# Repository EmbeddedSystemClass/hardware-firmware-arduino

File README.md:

hardware-firmware-arduino
=========================

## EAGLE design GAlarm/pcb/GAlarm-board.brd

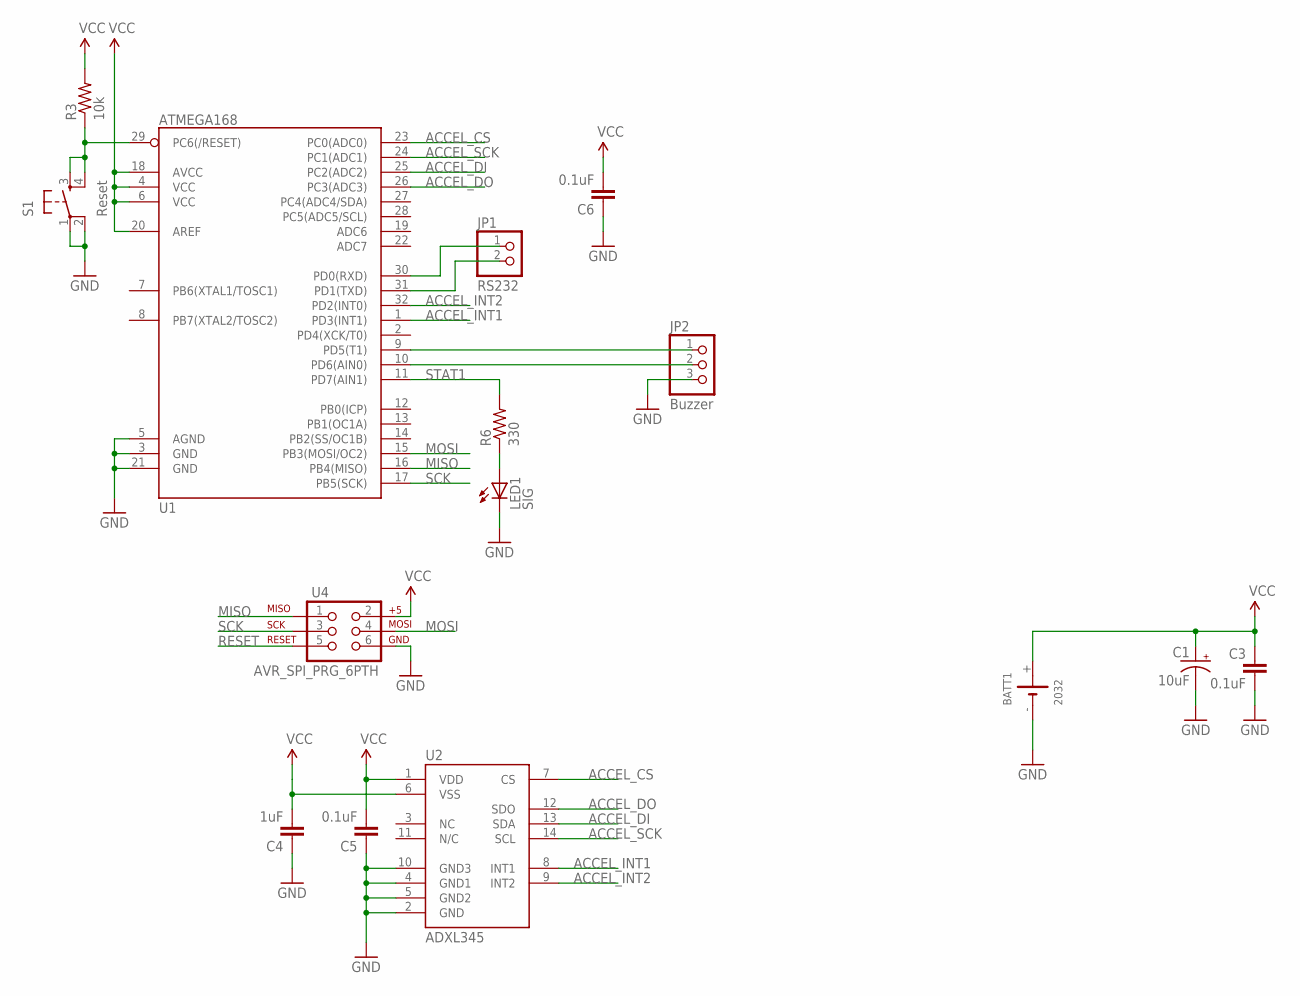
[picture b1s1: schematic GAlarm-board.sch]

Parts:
BATT1: 2032; 2032_SMD
C1: 10uF; EIA3216
C3, C5, C6: 0.1uF; 0603-CAP
C4: 1uF; 0805
JP1: RS232; 1X02
JP2: Buzzer; 1X03
LED1: SIG; LED-0603
R3: 10k; 0603-RES
R6: 330; 0603-RES
S1: Reset; TACTILE_SWITCH_SMD
U1: ATMEGA168; TQFP32-08
U2: ADXL345; LGA14
U4: AVR_SPI_PRG_6PTH; 2X3

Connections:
ACCEL_CS: U1.23 (PC0(ADC0)), U2.7 (CS)
ACCEL_DI: U1.25 (PC2(ADC2)), U2.13 (SDA)
ACCEL_DO: U1.26 (PC3(ADC3)), U2.12 (SDO)
ACCEL_INT1: U1.1 (PD3(INT1)), U2.8 (INT1)
ACCEL_INT2: U1.32 (PD2(INT0)), U2.9 (INT2)
ACCEL_SCK: U1.24 (PC1(ADC1)), U2.14 (SCL)
GND: BATT1.-, C1.C (-), C3.2, C4.1, C5.1, C6.1, JP2.3, LED1.C, S1.1, S1.2, U1.3 (GND), U1.5 (AGND), U1.21 (GND), U2.2 (GND), U2.4 (GND1), U2.5 (GND2), U2.10 (GND3), U4.6
MISO: U1.16 (PB4(MISO)), U4.1
MOSI: U1.15 (PB3(MOSI/OC2)), U4.4
unnamed: LED1.A, R6.1
unnamed: JP2.2, U1.10 (PD6(AIN0))
unnamed: JP1.1, U1.30 (PD0(RXD))
unnamed: JP1.2, U1.31 (PD1(TXD))
unnamed: JP2.1, U1.9 (PD5(T1))
RESET: R3.1, S1.3, S1.4, U1.29 (PC6(/RESET)), U4.5
SCK: U1.17 (PB5(SCK)), U4.3
STAT1: R6.2, U1.11 (PD7(AIN1))
VCC: BATT1.+, C1.A (+), C3.1, C4.2, C5.2, C6.2, R3.2, U1.4 (VCC), U1.6 (VCC), U1.18 (AVCC), U1.20 (AREF), U2.1 (VDD), U2.6 (VSS), U4.2

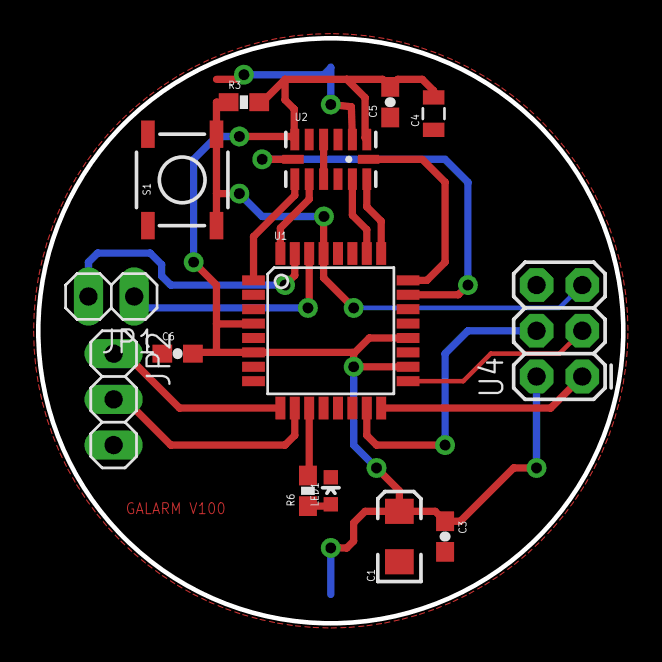
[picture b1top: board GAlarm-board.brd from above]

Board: 2 copper layers, 32.5 x 32.5 mm, 15 parts (1 on the bottom side), 18 nets.

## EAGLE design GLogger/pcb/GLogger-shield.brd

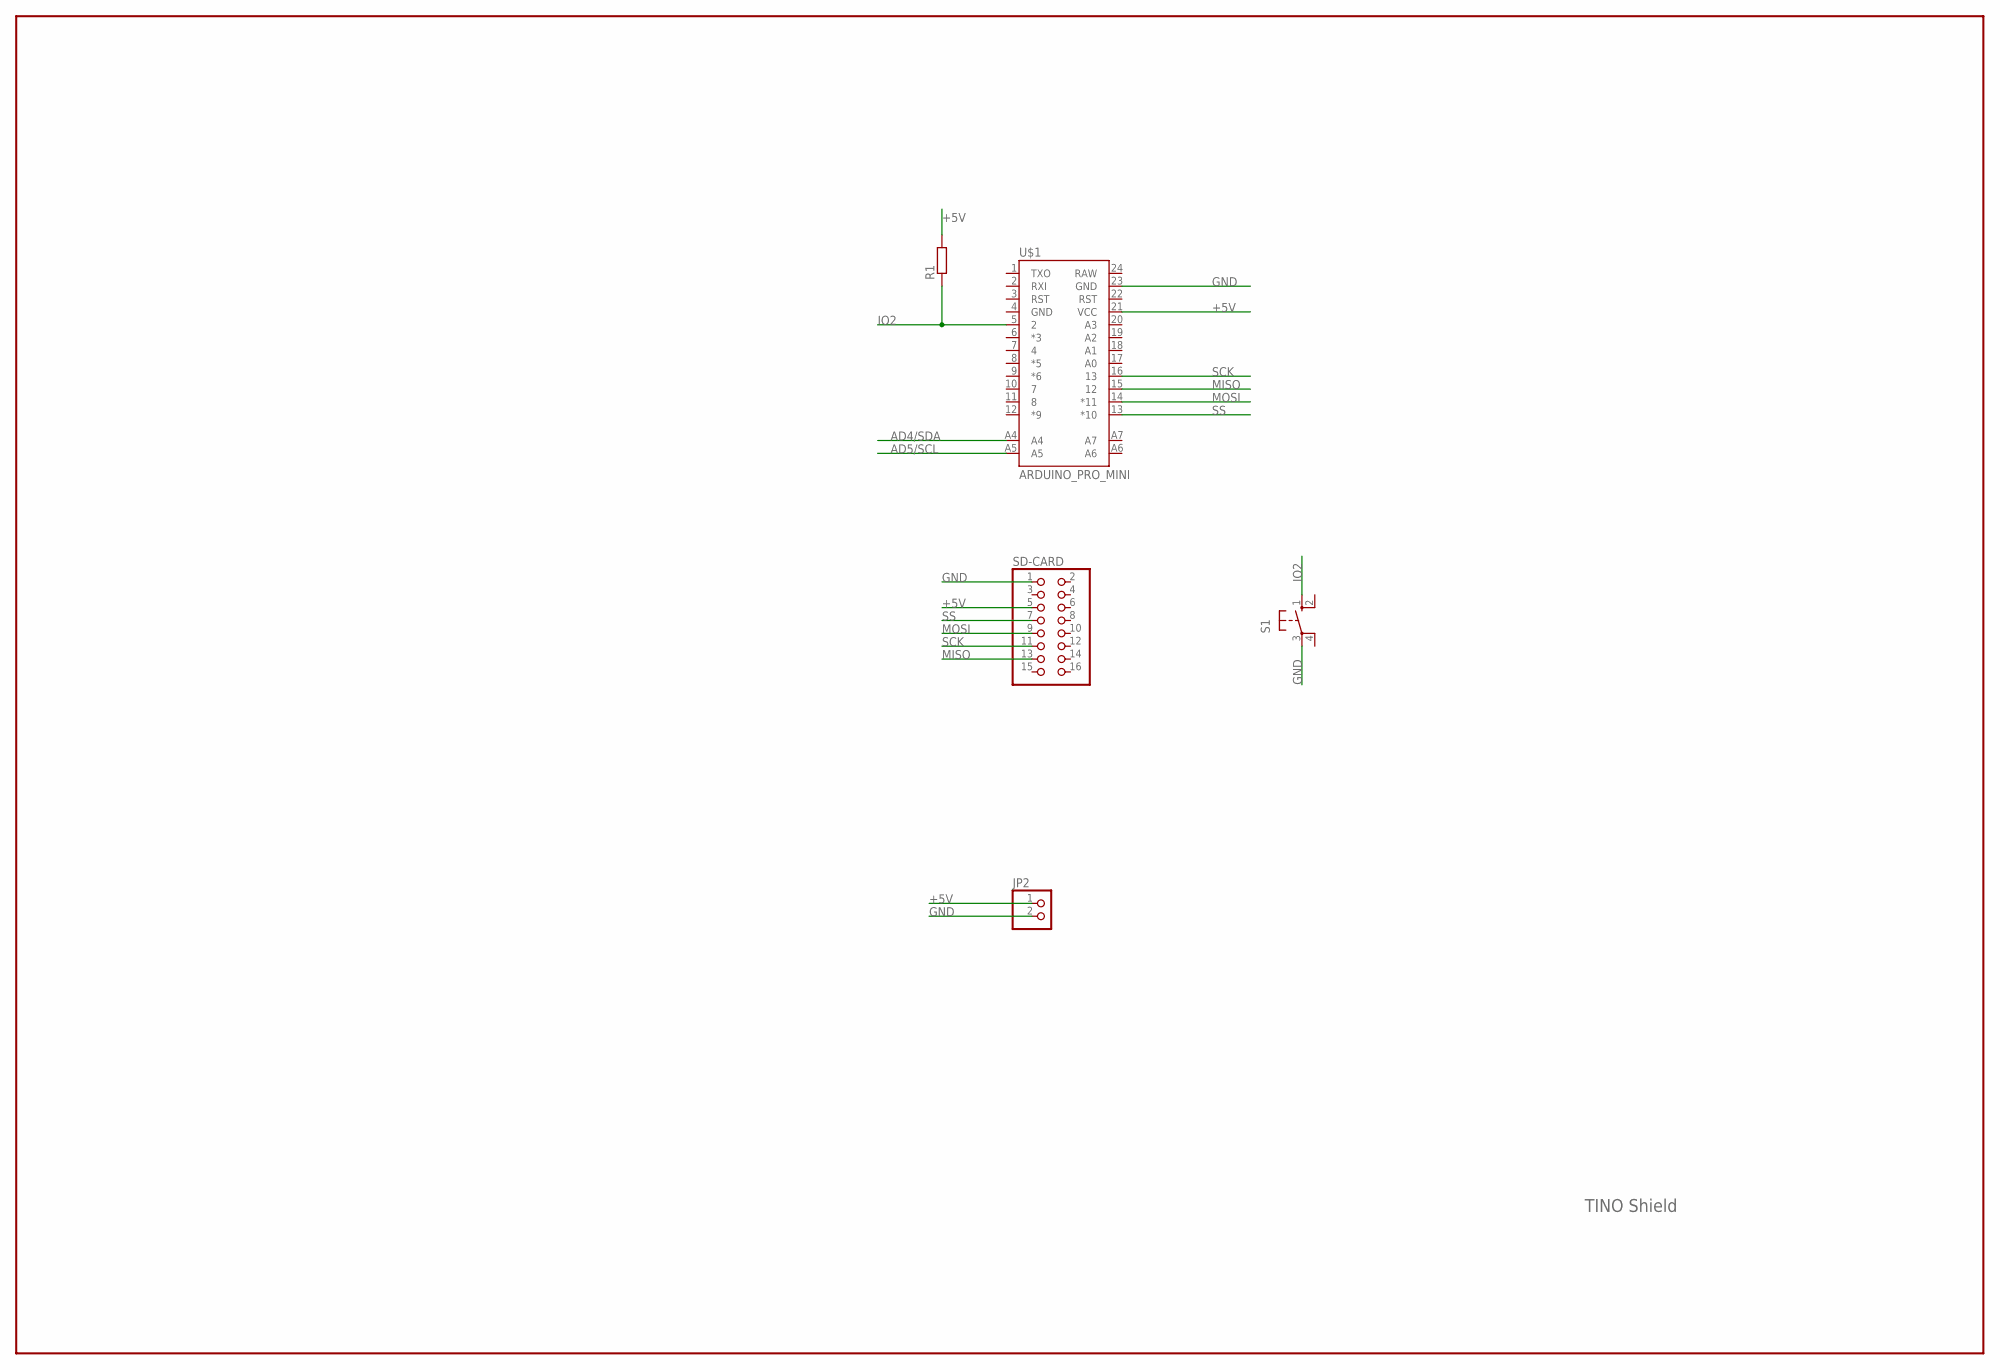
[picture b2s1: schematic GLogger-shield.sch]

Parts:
JP2: PINHD-1X2; 1X02
R1: R-EU_0207/10; 0207/10
S1: 40-XX-ROUND; B3F-40XX-ROUND
SD-CARD: PINHD-2X8; 2X08
U$1: ARDUINO_PRO_MINI

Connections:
+5V: JP2.1, R1.2, SD-CARD.5, U$1.21 (VCC)
AD4/SDA: U$1.A4
AD5/SCL: U$1.A5
GND: JP2.2, S1.3, SD-CARD.1, U$1.23 (GND)
IO2: R1.1, S1.1 (S), U$1.5 (2)
MISO: SD-CARD.13, U$1.15 (12)
MOSI: SD-CARD.9, U$1.14 (*11)
SCK: SD-CARD.11, U$1.16 (13)
SS: SD-CARD.7, U$1.13 (*10)

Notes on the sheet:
TINO Shield

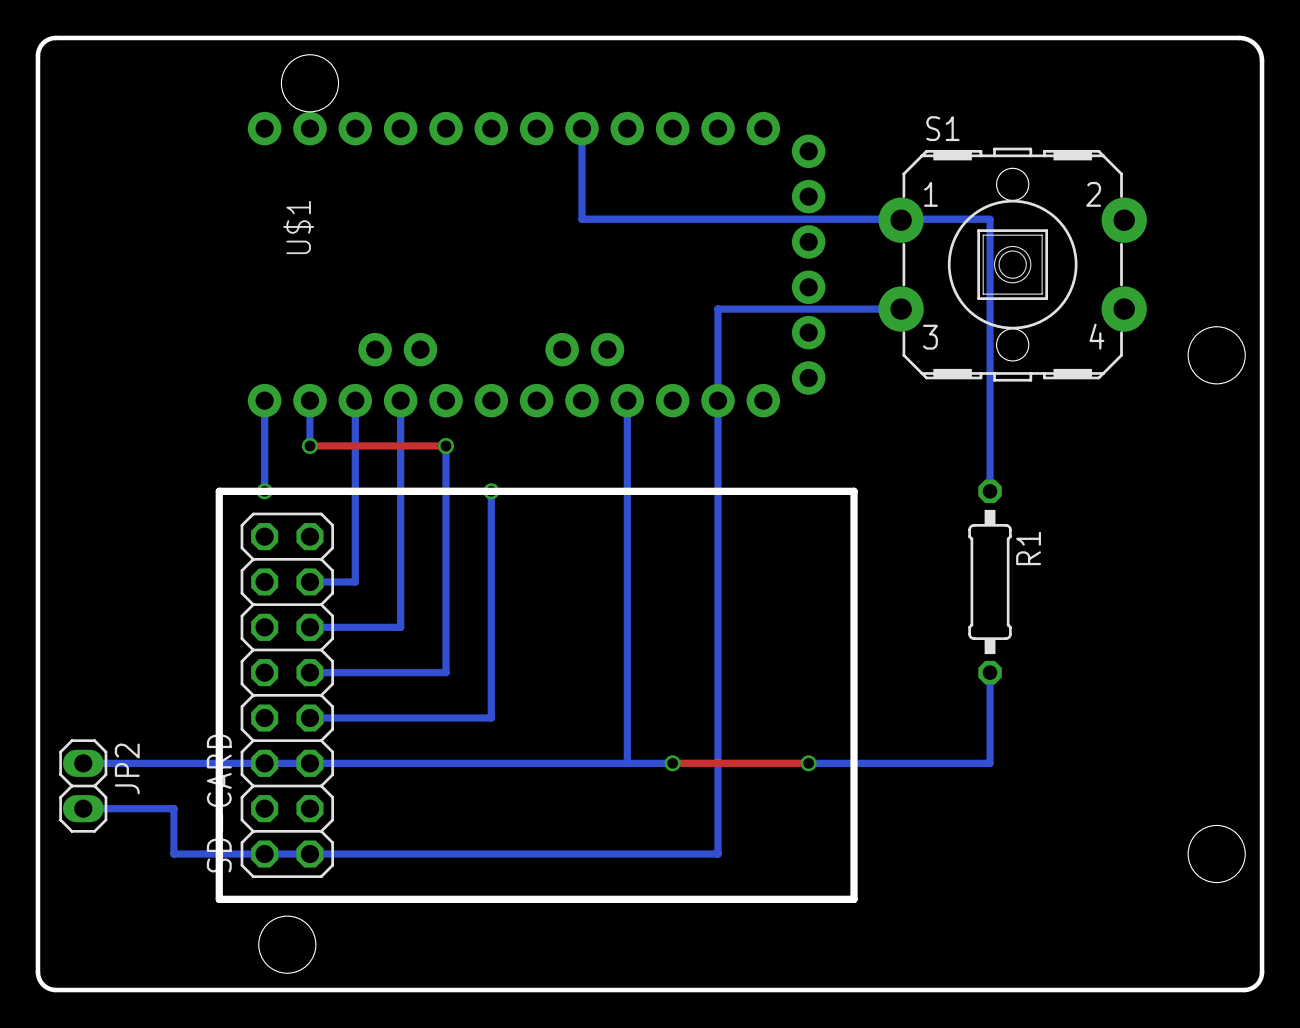
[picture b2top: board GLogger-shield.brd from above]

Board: 2 copper layers, 68.6 x 53.3 mm, 5 parts (0 on the bottom side), 7 nets.

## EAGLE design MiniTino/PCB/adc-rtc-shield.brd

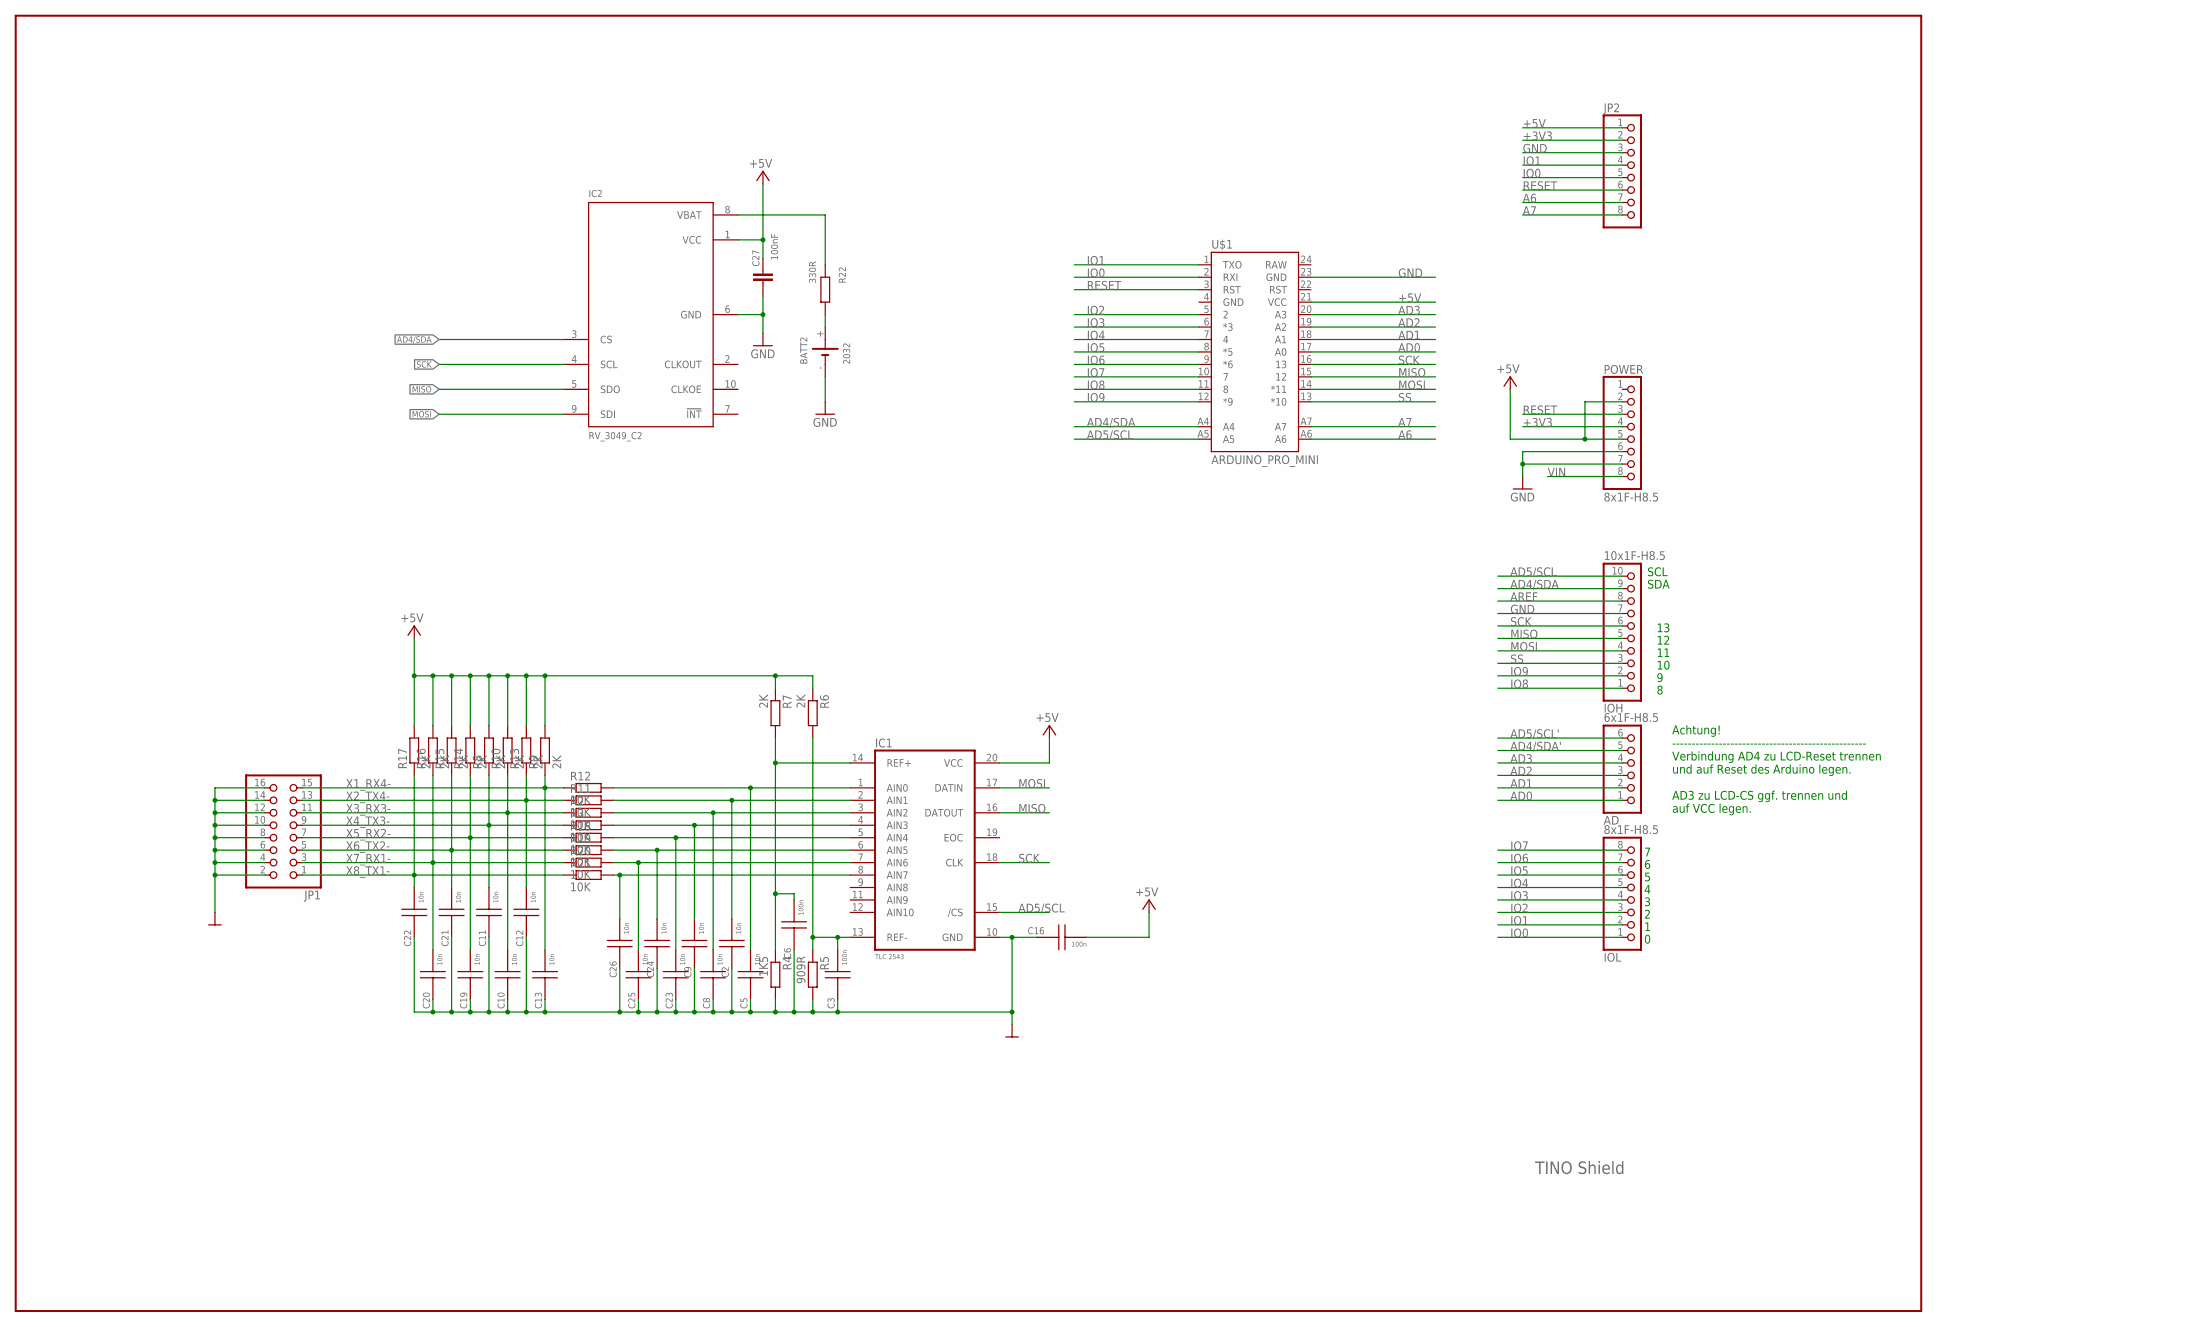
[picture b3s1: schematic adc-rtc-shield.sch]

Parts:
AD: 6x1F-H8.5; 1X06
BATT2: 2032; 2032_SMD
C2, C5, C8, C9, C10, C11, C12, C13, C19, C20, C21, C22, C23, C24, C25, C26: 10n; 0805-C
C3, C6, C16: 100n; 0805-C
C27: 100nF; C0603
IC1: TLC2543; DIL_20
IC2: RV_3049_C2; 5X3.2_10
IOH: 10x1F-H8.5; 1X10
IOL: 8x1F-H8.5; 1X08
JP1: PINHD-2X8/90; 2X08/90
JP2: PINHD-1X8/90; 1X08/90
POWER: 8x1F-H8.5; 1X08
R2, R3, R11, R12, R18, R19, R20, R21: 10K; R0603
R4: 1K5; R0603
R5: 909R; R0603
R6, R7, R8, R9, R10, R13, R14, R15, R16, R17: 2K; R0603
R22: 330R; R0603
U$1: ARDUINO_PRO_MINI

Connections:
+3V3: JP2.2, POWER.4
+5V: C16.2, C27.1, IC1.20 (VCC), IC2.1 (VCC), JP2.1, POWER.2, POWER.5, R6.1, R7.1, R8.2, R9.2, R10.2, R13.2, R14.2, R15.2, R16.2, R17.2, U$1.21 (VCC)
+BAT: BATT2.+, R22.1
A6: JP2.7, U$1.A6
A7: JP2.8, U$1.A7
AD0: AD.1, U$1.17 (A0)
AD1: AD.2, U$1.18 (A1)
AD2: AD.3, U$1.19 (A2)
AD3: AD.4, U$1.20 (A3)
AD4/SDA: IC2.3 (CS), IOH.9, U$1.A4
AD4/SDA': AD.5
AD5/SCL: IC1.15 (/CS), IOH.10, U$1.A5
AD5/SCL': AD.6
AREF: IOH.8
GND: BATT2.-, C2.1, C3.1, C5.1, C6.1, C8.1, C9.1, C10.1, C11.1, C12.1, C13.1, C16.1, C19.1, C20.1, C21.1, C22.1, C23.1, C24.1, C25.1, C26.1, C27.2, IC1.10 (GND), IC2.6 (GND), IOH.7, JP1.2, JP1.4, JP1.6, JP1.8, JP1.10, JP1.12, JP1.14, JP1.16, JP2.3, POWER.6, POWER.7, R4.2, R5.2, U$1.23 (GND)
IO0: IOL.1, JP2.5, U$1.2 (RXI)
IO1: IOL.2, JP2.4, U$1.1 (TXO)
IO2: IOL.3, U$1.5 (2)
IO3: IOL.4, U$1.6 (*3)
IO4: IOL.5, U$1.7 (4)
IO5: IOL.6, U$1.8 (*5)
IO6: IOL.7, U$1.9 (*6)
IO7: IOL.8, U$1.10 (7)
IO8: IOH.1, U$1.11 (8)
IO9: IOH.2, U$1.12 (*9)
MISO: IC1.16 (DATOUT), IC2.5 (SDO), IOH.5, U$1.15 (12)
MOSI: IC1.17 (DATIN), IC2.9 (SDI), IOH.4, U$1.14 (*11)
unnamed: C3.2, IC1.13 (REF-), R5.1, R6.2
unnamed: C6.2, IC1.14 (REF+), R4.1, R7.2
unnamed: C2.2, IC1.2 (AIN1), R11.2
unnamed: C8.2, IC1.3 (AIN2), R2.2
unnamed: C9.2, IC1.4 (AIN3), R3.2
unnamed: C5.2, IC1.1 (AIN0), R12.2
unnamed: C23.2, IC1.5 (AIN4), R18.2
unnamed: C24.2, IC1.6 (AIN5), R19.2
unnamed: C25.2, IC1.7 (AIN6), R20.2
unnamed: C26.2, IC1.8 (AIN7), R21.2
unnamed: IC2.8 (VBAT), R22.2
RESET: JP2.6, POWER.3, U$1.3 (RST)
SCK: IC1.18 (CLK), IC2.4 (SCL), IOH.6, U$1.16 (13)
SS: IOH.3, U$1.13 (*10)
VIN: POWER.8
X1_RX4-: C13.2, JP1.15, R9.1, R12.1
X2_TX4-: C12.2, JP1.13, R11.1, R13.1
X3_RX3-: C10.2, JP1.11, R2.1, R10.1
X4_TX3-: C11.2, JP1.9, R3.1, R8.1
X5_RX2-: C19.2, JP1.7, R14.1, R18.1
X6_TX2-: C21.2, JP1.5, R15.1, R19.1
X7_RX1-: C20.2, JP1.3, R16.1, R20.1
X8_TX1-: C22.2, JP1.1, R17.1, R21.1

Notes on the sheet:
SDA
SCL
TINO Shield
Achtung! -------------------------------------------------- Verbindung AD4 zu LCD-Reset trennen und auf Reset des Arduino legen. AD3 zu LCD-CS ggf. trennen und auf VCC legen.

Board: 2 copper layers, 51 parts (32 on the bottom side), 46 nets, no tracks yet.

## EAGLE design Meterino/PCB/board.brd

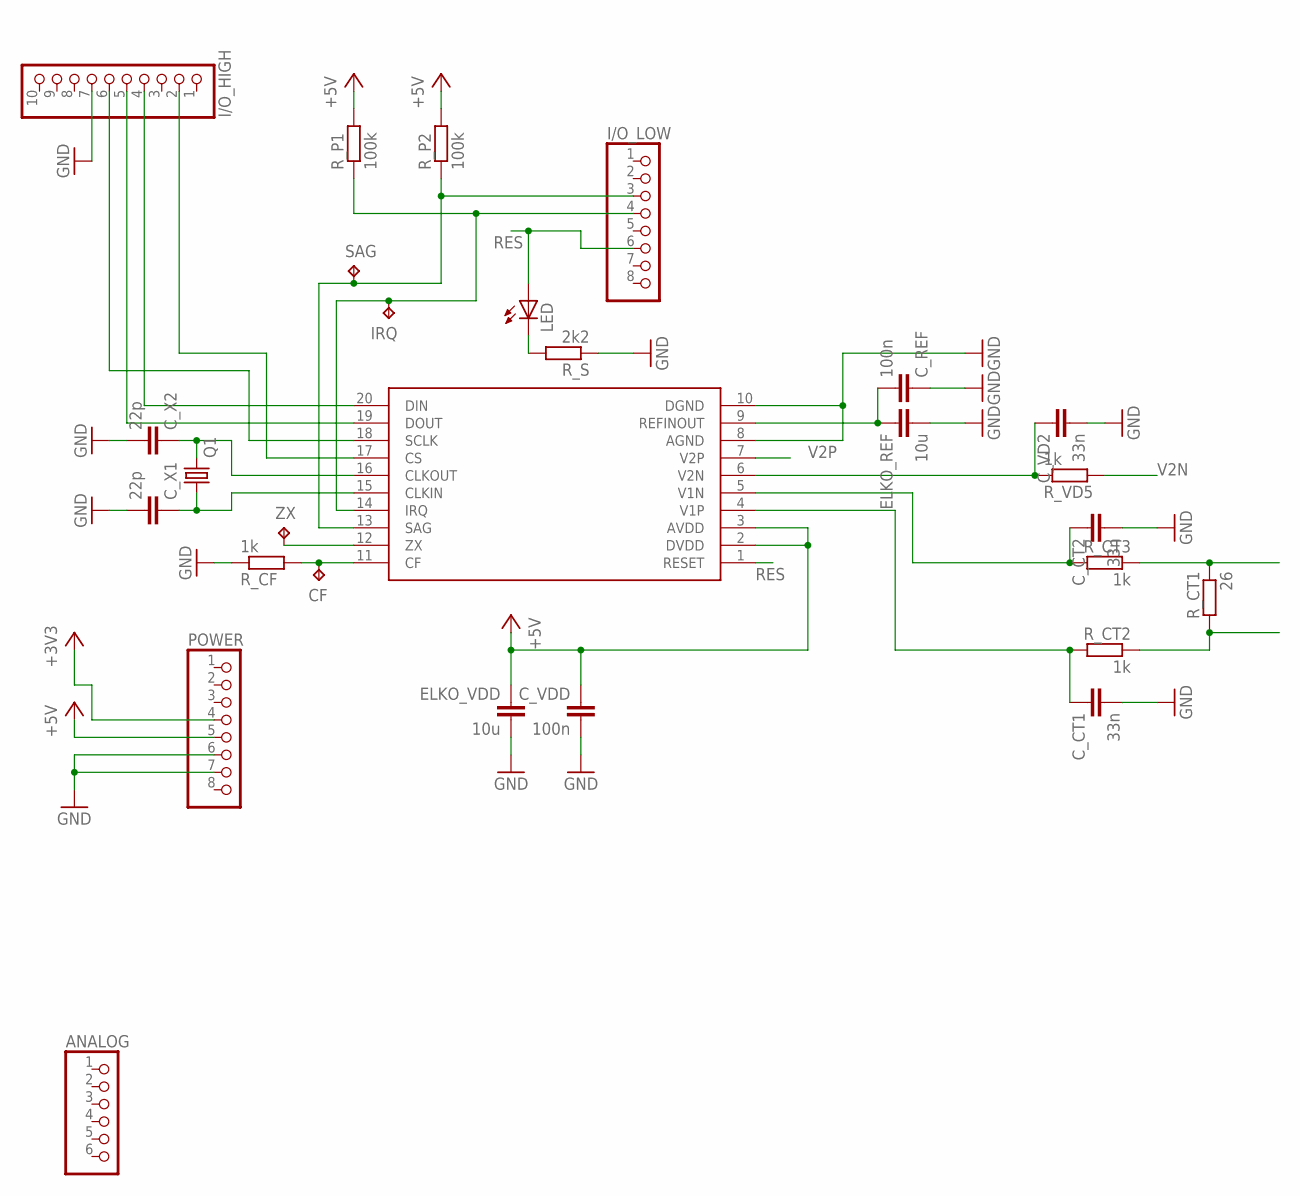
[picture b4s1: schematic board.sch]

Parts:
ANALOG: PINHD-1X6; 1X06
CF: TPPAD1-17; P1-17
C_CT1, C_CT2: 33n; C1206K
C_REF: 100n; C1206K
C_VD2: 33n; C1206K
C_VDD: 100n; C1206K
C_X1, C_X2: 22p; C1206K
ELKO_REF: 10u; C7.5B3
ELKO_VDD: 10u; C7.5B3
I/O_HIGH: PINHD-1X10TH; 1X10-TH
I/O_LOW: PINHD-1X8TH; 1X08-TH
IRQ: TPPAD1-17; P1-17
LED: LED3MM
POWER: PINHD-1X8TH; 1X08-TH
Q1: CRYSTALHC18U-V; HC18U-V
R_CF: 1k; R2010
R_CT1: 26; R2512
R_CT2, R_CT3: 1k; R2010
R_P1, R_P2: 100k; R2010
R_S: 2k2; R2512
R_VD5: 1k; R2010
SAG: TPPAD1-17; P1-17
U$1: ADE7753; SSOP20
ZX: TPPAD1-17; P1-17

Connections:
+3V3: POWER.4
+5V: C_VDD.1, ELKO_VDD.1, POWER.5, R_P1.2, R_P2.2, U$1.2 (DVDD), U$1.3 (AVDD)
GND: C_CT1.2, C_CT2.2, C_REF.1, C_VD2.2, C_VDD.2, C_X1.2, C_X2.2, ELKO_REF.2, ELKO_VDD.2, I/O_HIGH.7, POWER.6, POWER.7, R_CF.1, R_S.1, U$1.8 (AGND), U$1.10 (DGND)
unnamed: I/O_HIGH.6, U$1.18 (SCLK)
unnamed: I/O_HIGH.4, U$1.20 (DIN)
unnamed: I/O_LOW.4, IRQ.TP, R_P1.1, U$1.14 (IRQ)
unnamed: I/O_HIGH.2, U$1.17 (CS)
unnamed: C_REF.2, ELKO_REF.1, U$1.9 (REFINOUT)
unnamed: I/O_LOW.3, R_P2.1, SAG.TP, U$1.13 (SAG)
unnamed: R_CT1.2, R_CT2.1
unnamed: I/O_HIGH.5, U$1.19 (DOUT)
unnamed: LED.K (C), R_S.2
unnamed: U$1.12 (ZX), ZX.TP
unnamed: C_VD2.1, R_VD5.1, U$1.6 (V2N)
unnamed: CF.TP, R_CF.2, U$1.11 (CF)
unnamed: R_CT1.1, R_CT3.1
unnamed: C_CT2.1, R_CT3.2, U$1.5 (V1N)
unnamed: C_CT1.1, R_CT2.2, U$1.4 (V1P)
unnamed: C_X1.1, Q1.1, U$1.15 (CLKIN)
unnamed: C_X2.1, Q1.2, U$1.16 (CLKOUT)
RES: I/O_LOW.6, LED.A, U$1.1 (RESET)
V2N: R_VD5.2
V2P: U$1.7 (V2P)

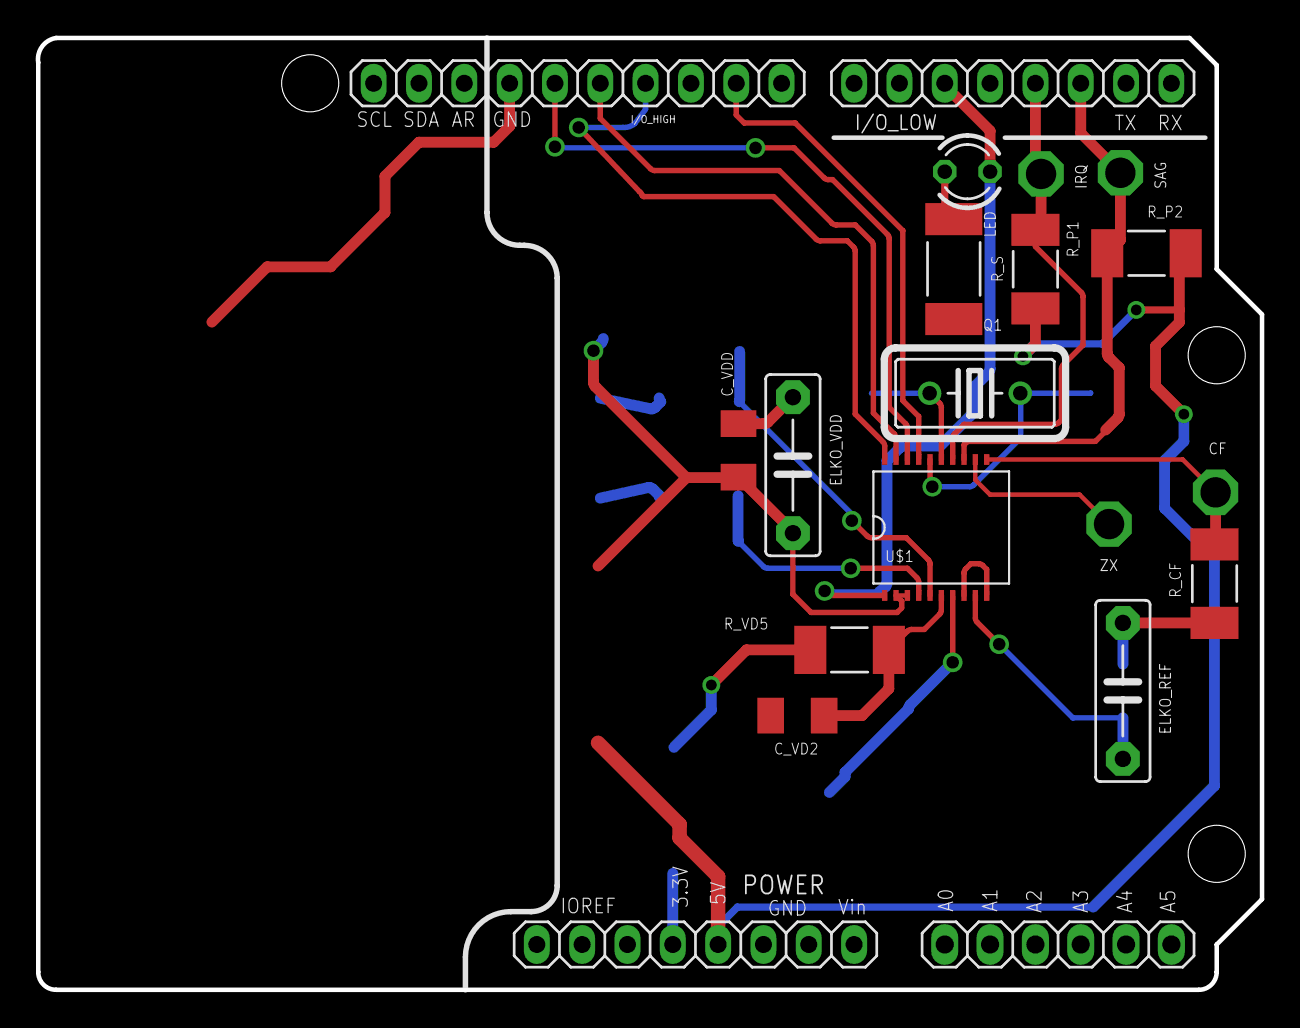
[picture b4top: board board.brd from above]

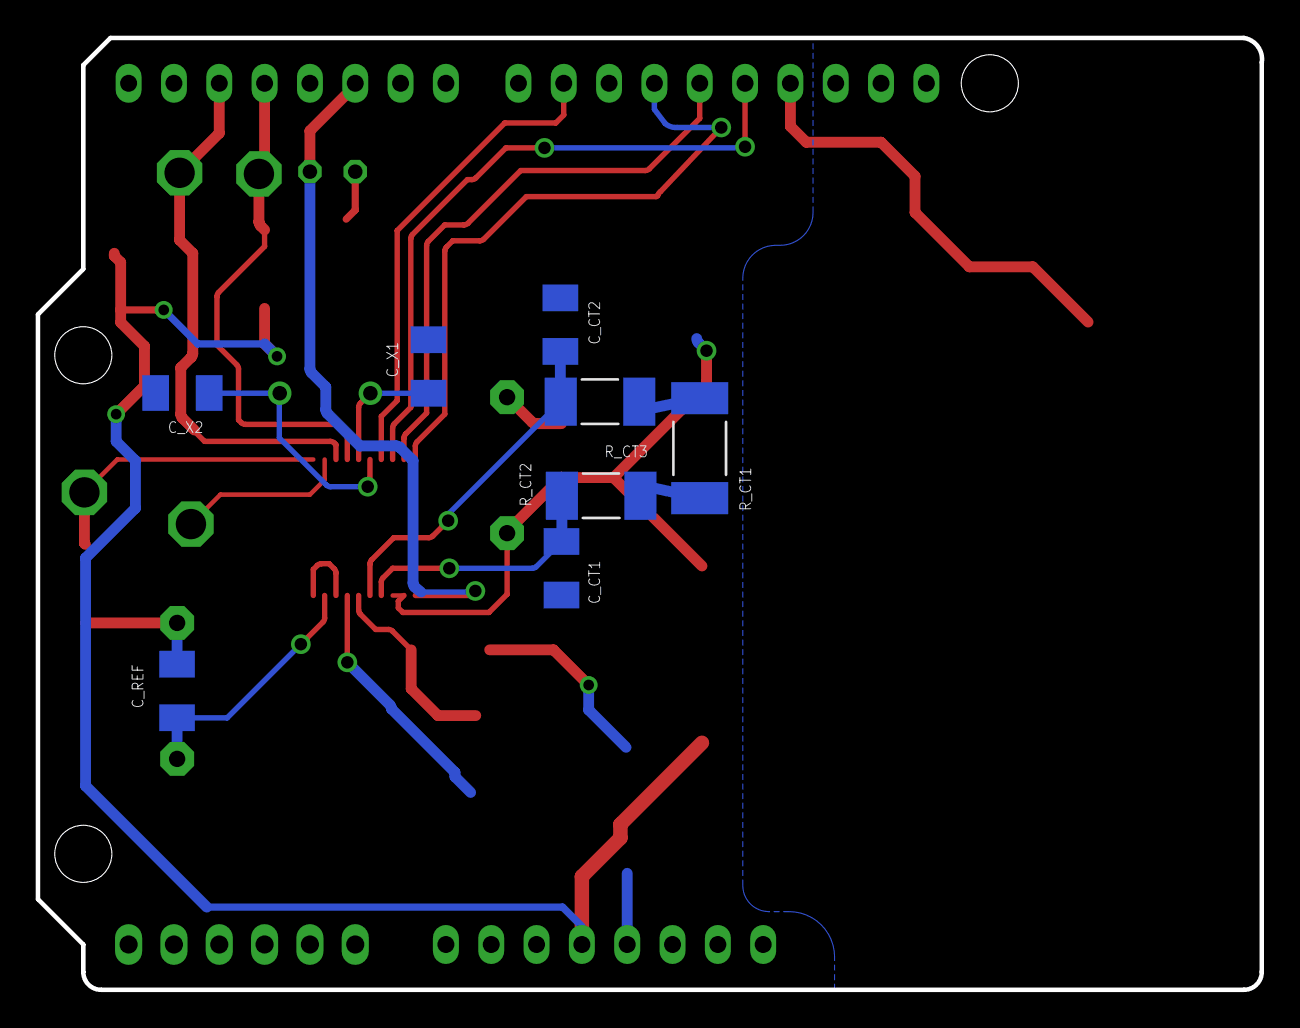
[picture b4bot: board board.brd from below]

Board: 2 copper layers, 68.6 x 53.3 mm, 28 parts (8 on the bottom side), 20 nets.

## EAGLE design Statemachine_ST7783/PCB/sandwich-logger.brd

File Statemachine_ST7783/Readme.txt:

-Display ST7783
-Temperature Sensor DS1621

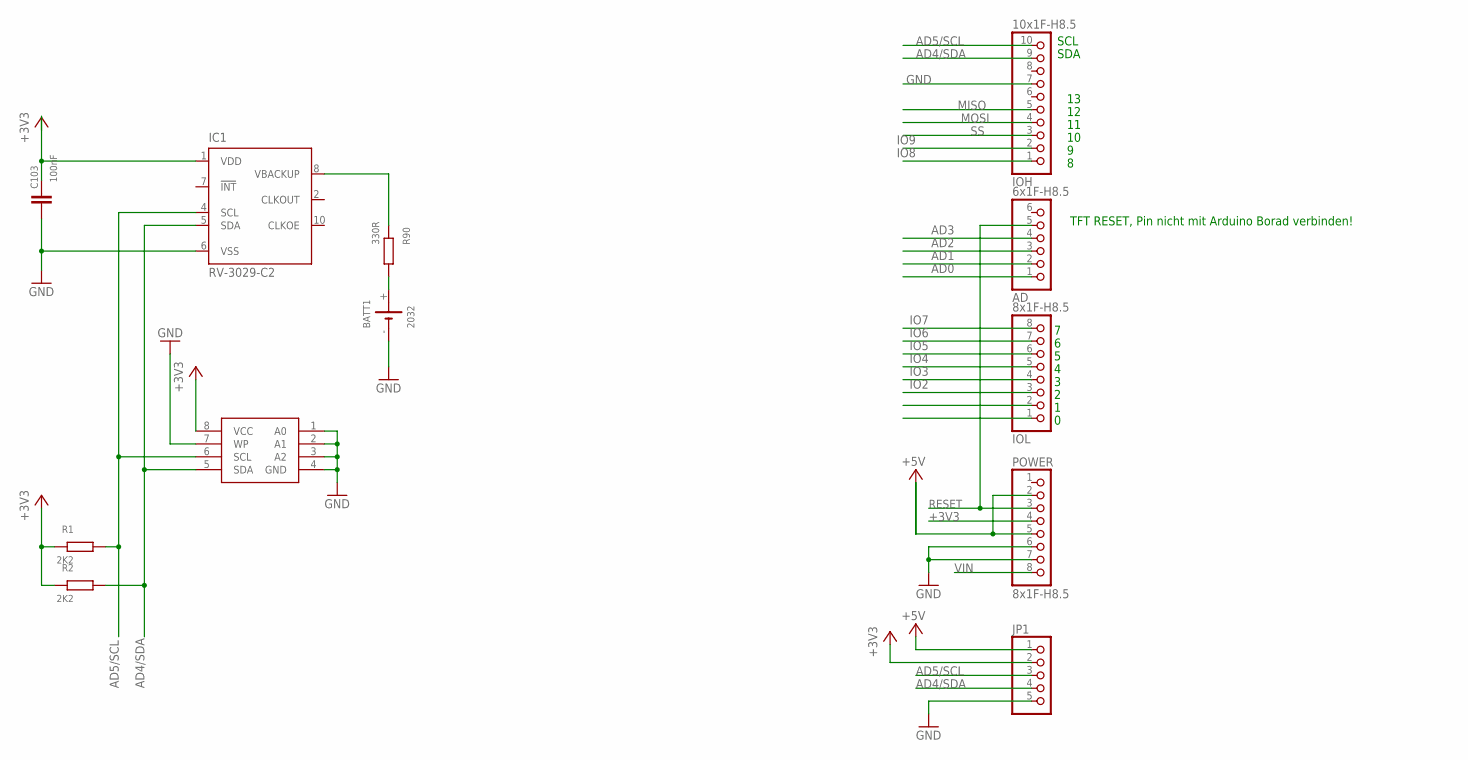
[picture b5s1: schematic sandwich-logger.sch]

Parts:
AD: 6x1F-H8.5; 1X06
BATT1: 2032; 2032_SMD
C103: 100nF; C0603
IC1: RV-3029-C2; SON-10
IC3: AT24C32; SOIC08
IOH: 10x1F-H8.5; 1X10
IOL: 8x1F-H8.5; 1X08
JP1: PINHD-1X5/90; 1X05/90
POWER: 8x1F-H8.5; 1X08
R1, R2: 2K2; R0603
R90: 330R; R0603

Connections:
+3V3: C103.1, IC1.1 (VDD), IC3.8 (VCC), JP1.2, POWER.4, R1.2, R2.2
+5V: JP1.1, POWER.2, POWER.5
AD0: AD.1
AD1: AD.2
AD2: AD.3
AD3: AD.4
AD4/SDA: IC1.5 (SDA), IC3.5 (SDA), IOH.9, JP1.4, R2.1
AD5/SCL: IC1.4 (SCL), IC3.6 (SCL), IOH.10, JP1.3, R1.1
GND: BATT1.-, C103.2, IC1.6 (VSS), IC3.1 (A0), IC3.2 (A1), IC3.3 (A2), IC3.4 (GND), IC3.7 (WP), IOH.7, JP1.5, POWER.6, POWER.7
IO2: IOL.3
IO3: IOL.4
IO4: IOL.5
IO5: IOL.6
IO6: IOL.7
IO7: IOL.8
IO8: IOH.1
IO9: IOH.2
MISO: IOH.5
MOSI: IOH.4
unnamed: BATT1.+, R90.1
unnamed: IC1.8 (VBACKUP), R90.2
RESET: AD.5, POWER.3
SS: IOH.3
VIN: POWER.8

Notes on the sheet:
SDA
SCL
TFT RESET, Pin nicht mit Arduino Borad verbinden!

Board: 2 copper layers, 12 parts (0 on the bottom side), 8 nets, no tracks yet.

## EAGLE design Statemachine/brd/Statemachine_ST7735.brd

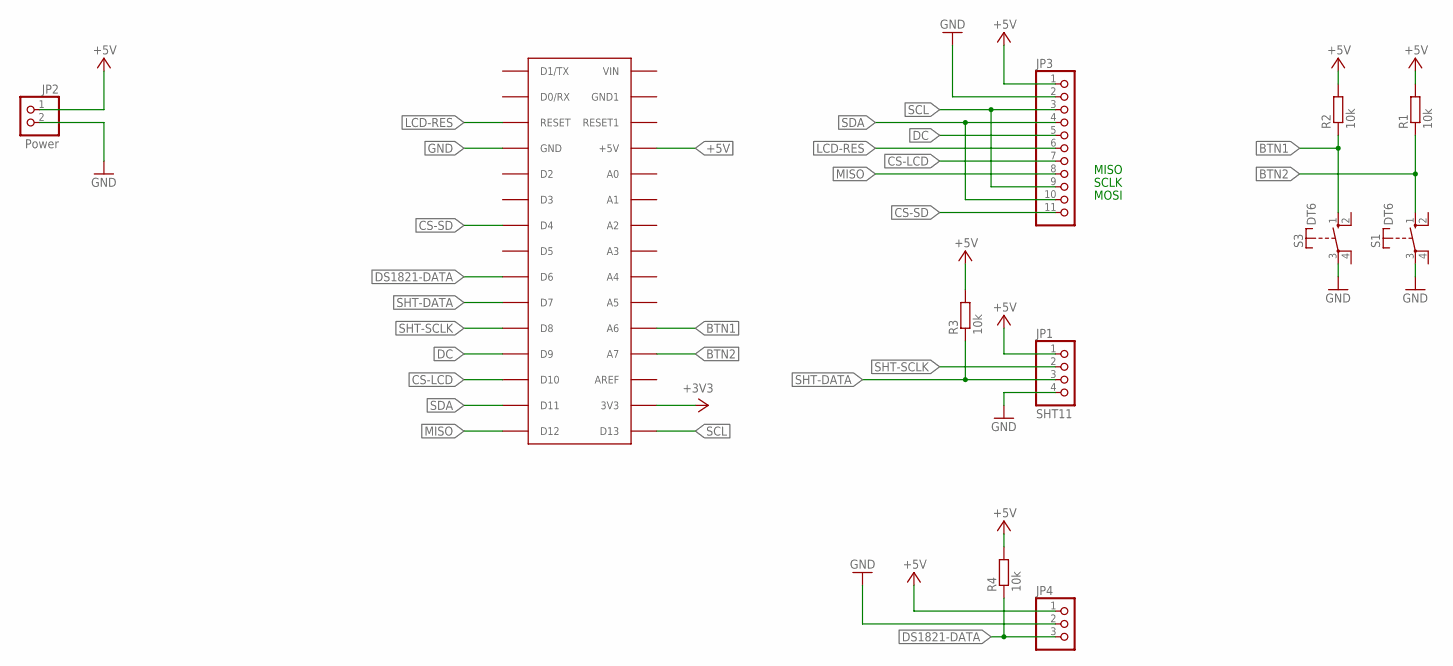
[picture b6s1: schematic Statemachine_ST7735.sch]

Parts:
JP1: SHT11; 1X04
JP2: Power; 1X02
JP3: PINHD-1X11; 1X11
JP4: PINHD-1X3; 1X03
R1, R4: 10k; 0207/10
R2, R3: 10k; 0204/7
S1, S3: DT6
U$1: ARDUINONANO; PDIP-32

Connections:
+3V3: U$1.3V3
+5V: JP1.1, JP2.1, JP3.1, JP4.1, R1.2, R2.2, R3.2, R4.2, U$1.+5V
BTN1: R2.1, S3.1 (S), U$1.A6
BTN2: R1.1, S1.1 (S), U$1.A7
CS-LCD: JP3.7, U$1.D10
CS-SD: JP3.11, U$1.D4
DC: JP3.5, U$1.D9
DS1821-DATA: JP4.3, R4.1, U$1.D6
GND: JP1.4, JP2.2, JP3.2, JP4.2, S1.3, S3.3, U$1.GND
LCD-RES: JP3.6, U$1.RESET
MISO: JP3.8, U$1.D12
SCL: JP3.3, JP3.9, U$1.D13
SDA: JP3.4, JP3.10, U$1.D11
SHT-DATA: JP1.3, R3.1, U$1.D7
SHT-SCLK: JP1.2, U$1.D8

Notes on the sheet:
MISO
SCLK
MOSI

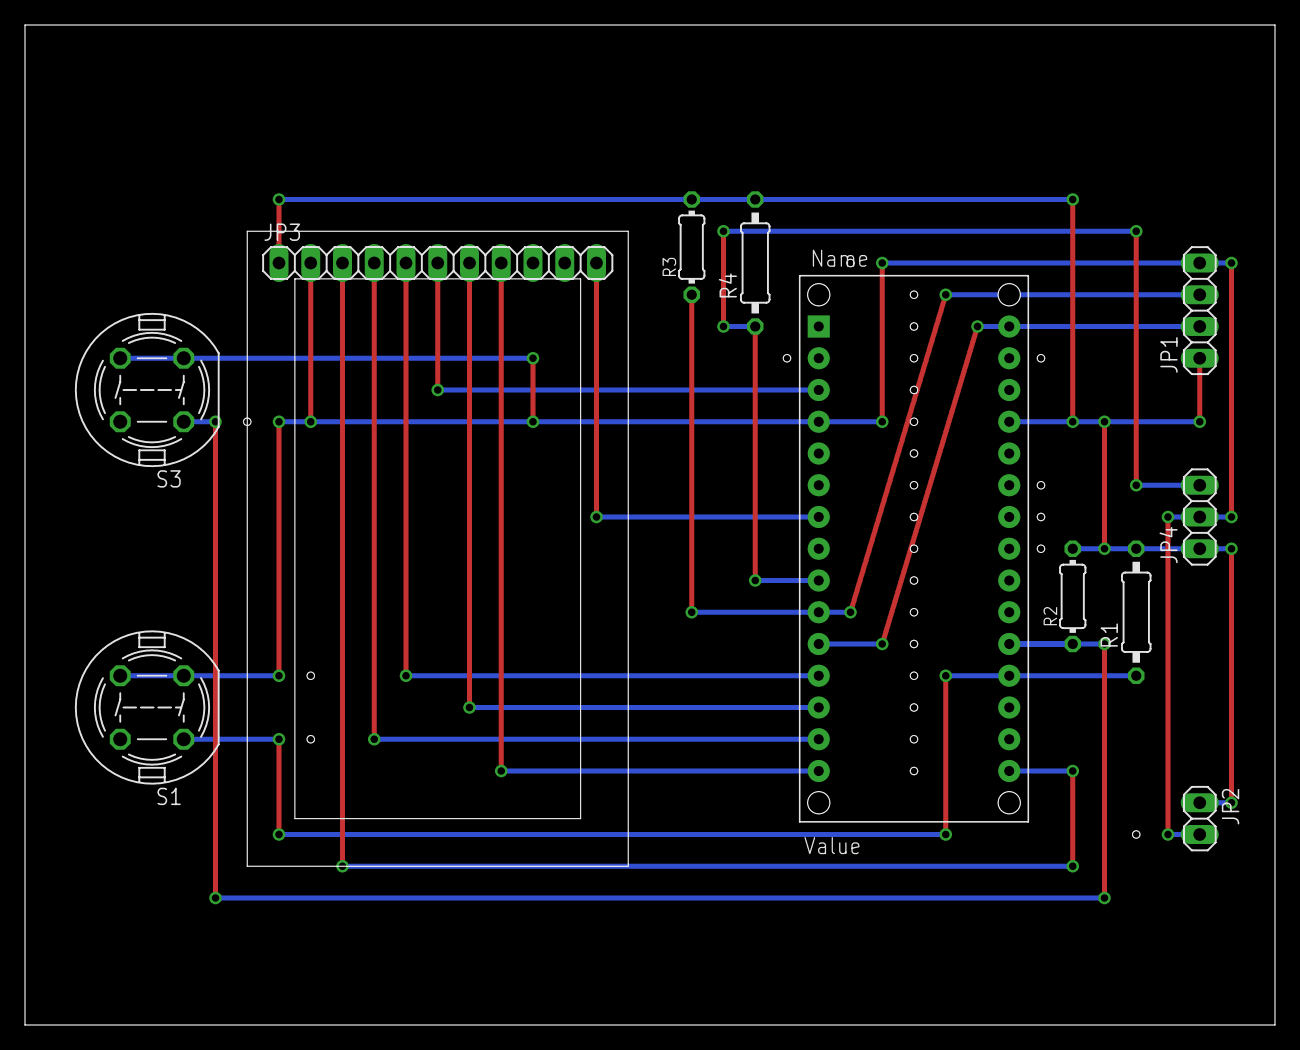
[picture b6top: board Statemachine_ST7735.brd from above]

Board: 2 copper layers, 100.0 x 80.0 mm, 11 parts (0 on the bottom side), 14 nets.

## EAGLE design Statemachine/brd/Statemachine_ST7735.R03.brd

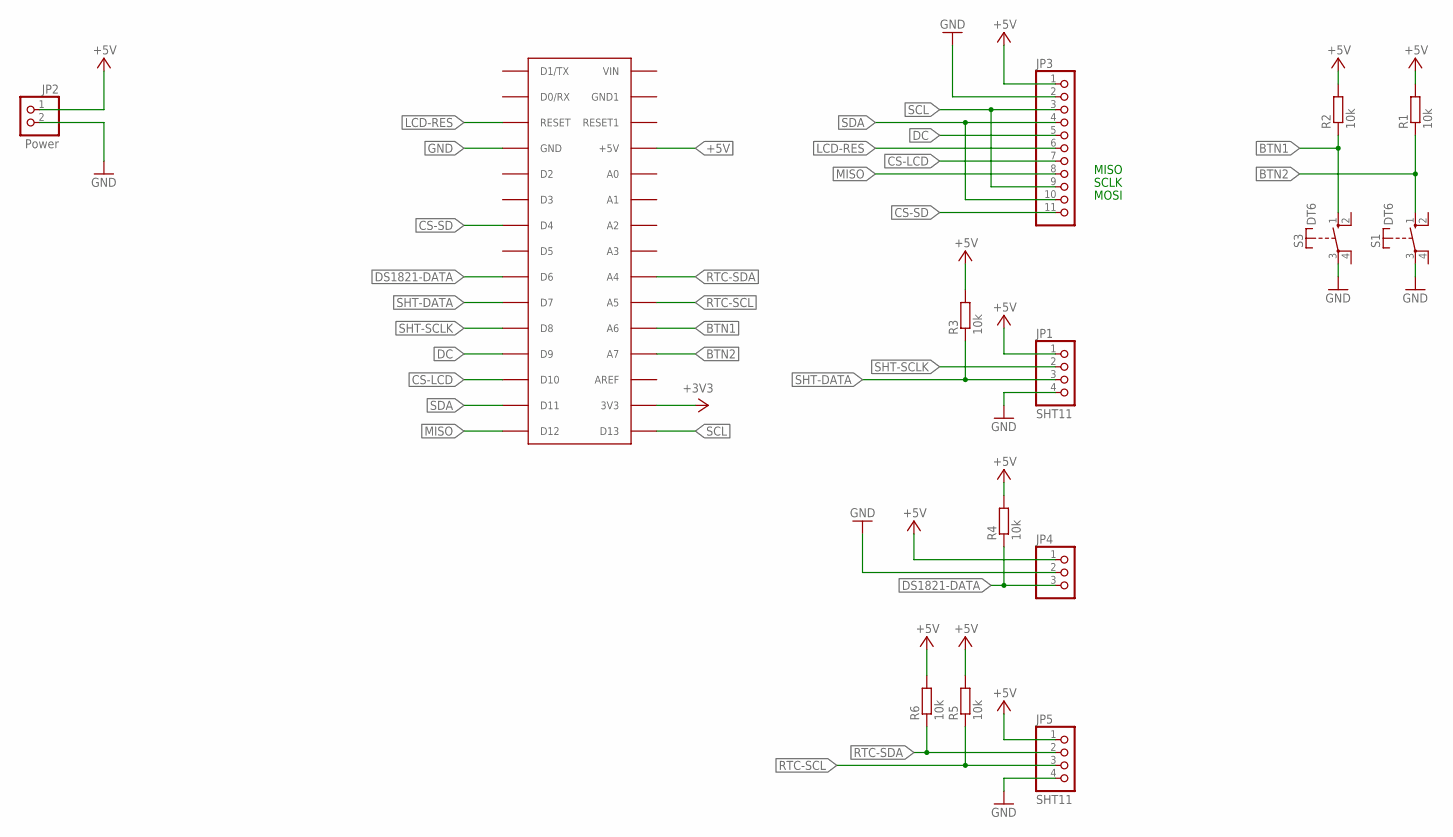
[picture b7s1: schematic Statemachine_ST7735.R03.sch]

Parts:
JP1, JP5: SHT11; 1X04
JP2: Power; 1X02
JP3: PINHD-1X11; 1X11
JP4: PINHD-1X3; 1X03
NANO: ARDUINONANO; PDIP-32
R1, R2, R3, R4, R5, R6: 10k; 0204/7
S1, S3: DT6

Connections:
+3V3: NANO.3V3
+5V: JP1.1, JP2.1, JP3.1, JP4.1, JP5.1, NANO.+5V, R1.2, R2.2, R3.2, R4.2, R5.2, R6.2
BTN1: NANO.A6, R2.1, S3.1 (S)
BTN2: NANO.A7, R1.1, S1.1 (S)
CS-LCD: JP3.7, NANO.D10
CS-SD: JP3.11, NANO.D4
DC: JP3.5, NANO.D9
DS1821-DATA: JP4.3, NANO.D6, R4.1
GND: JP1.4, JP2.2, JP3.2, JP4.2, JP5.4, NANO.GND, S1.3, S3.3
LCD-RES: JP3.6, NANO.RESET
MISO: JP3.8, NANO.D12
RTC-SCL: JP5.3, NANO.A5, R5.1
RTC-SDA: JP5.2, NANO.A4, R6.1
SCL: JP3.3, JP3.9, NANO.D13
SDA: JP3.4, JP3.10, NANO.D11
SHT-DATA: JP1.3, NANO.D7, R3.1
SHT-SCLK: JP1.2, NANO.D8

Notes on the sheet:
MISO
SCLK
MOSI

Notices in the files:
parts and their libraries:
SparkFun-Boards: Licensing: Creative Commons ShareAlike 4.0 International - https://creativecommons.org/licenses/by-sa/4.0
